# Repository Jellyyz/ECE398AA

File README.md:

<h1>Final Project</h1>

<h1>Midterm Project</h1>

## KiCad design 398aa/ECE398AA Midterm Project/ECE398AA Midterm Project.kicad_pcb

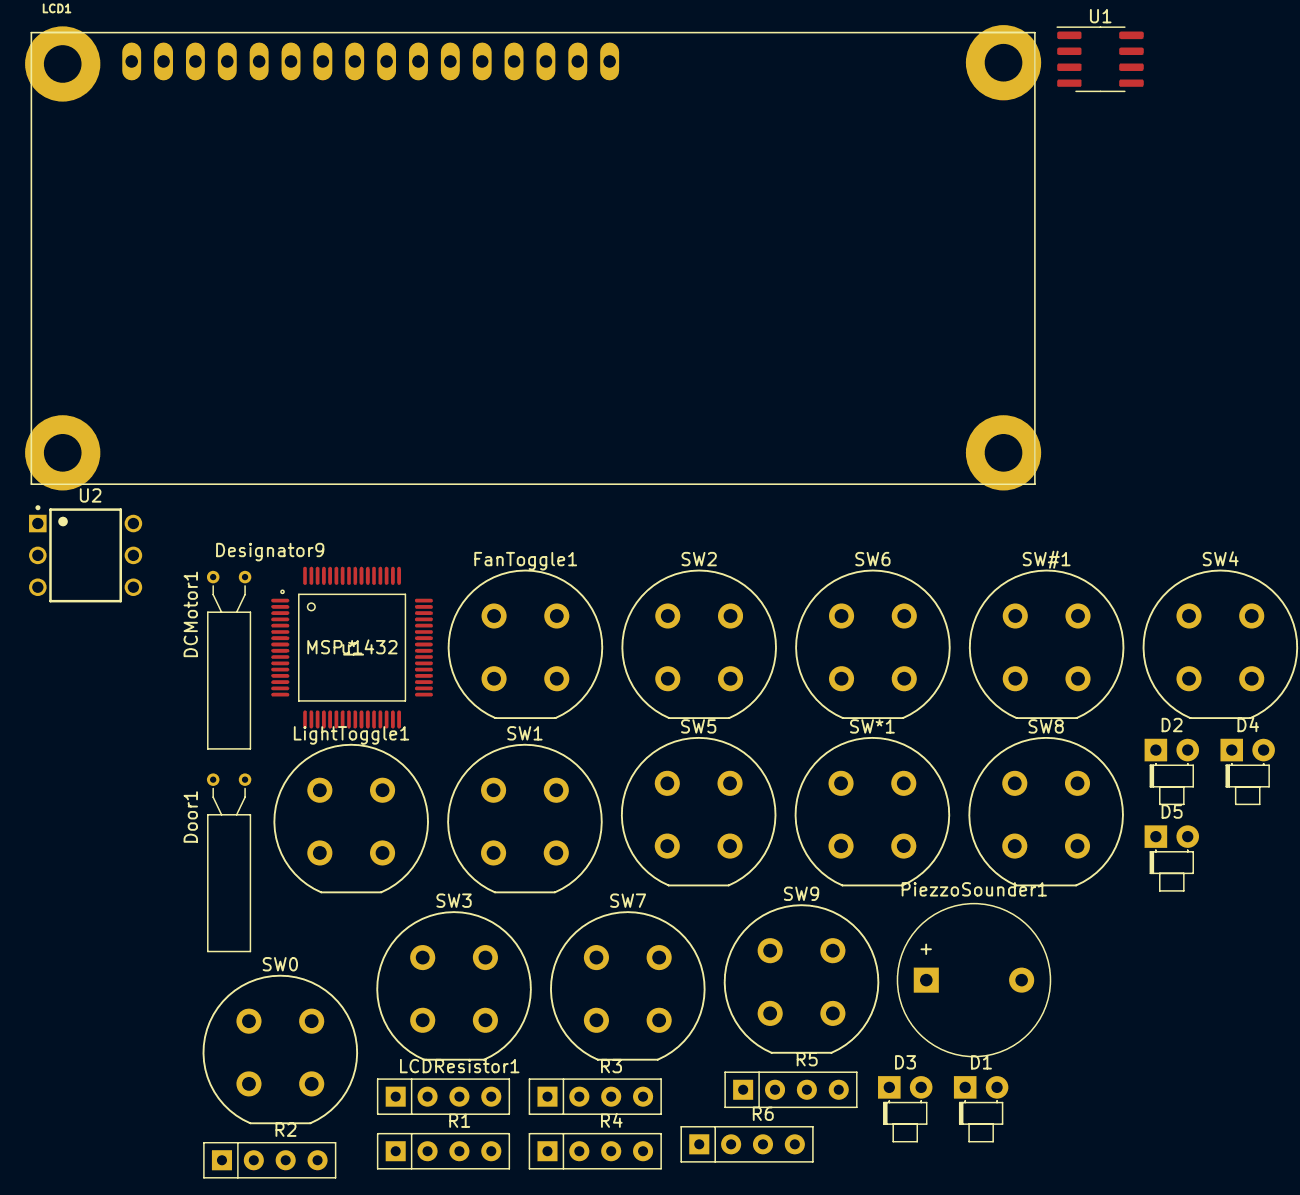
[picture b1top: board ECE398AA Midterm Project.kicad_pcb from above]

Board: 2 copper layers, 33 parts (0 on the bottom side), 14 nets, no tracks yet.

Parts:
D1, D2, D3: Yellow (House Lights); LED_D1.8mm_W1.8mm_H2.4mm_Horizontal_O1.27mm_Z1.6mm
D4: Door Open (Green); LED_D1.8mm_W1.8mm_H2.4mm_Horizontal_O1.27mm_Z1.6mm
D5: Door Close (Red); LED_D1.8mm_W1.8mm_H2.4mm_Horizontal_O1.27mm_Z1.6mm
DCMotor1: Fan1; Crystal_AT310_D3.0mm_L10.0mm_Horizontal
Door1: Motor_Servo; Crystal_AT310_D3.0mm_L10.0mm_Horizontal
FanToggle1: SW_Push; Push_E-Switch_KS01Q01
LCD1: HD44780; 16026-16X2
LCDResistor1: R_POT_US; R_Array_SIP4
LightToggle1: SW_Push; Push_E-Switch_KS01Q01
PiezzoSounder1: Buzzer; Buzzer_12x9.5RM7.6
R1, R2, R3, R4, R5: 330 Ω; R_Array_SIP4
R6: 300 Ω; R_Array_SIP4
SW0: 0; Push_E-Switch_KS01Q01
SW1: 1; Push_E-Switch_KS01Q01
SW2: 2; Push_E-Switch_KS01Q01
SW3: 3; Push_E-Switch_KS01Q01
SW4: 4; Push_E-Switch_KS01Q01
SW5: 5; Push_E-Switch_KS01Q01
SW6: 6; Push_E-Switch_KS01Q01
SW7: 7; Push_E-Switch_KS01Q01
SW8: 8; Push_E-Switch_KS01Q01
SW9: 9; Push_E-Switch_KS01Q01
SW#1: #; Push_E-Switch_KS01Q01
SW*1: *; Push_E-Switch_KS01Q01
U1: TMP36xS; SOIC-8_3.9x4.9mm_P1.27mm
U2: H11B1; DIP762W50P254L730H410Q6
u1: MSP__432; MSP430FR5994IPM

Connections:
GNDREF: D1.1, D2.1, D3.1, D4.1, D5.1
unnamed: D1.2, R1.2
unnamed: D2.2, R2.2
unnamed: D3.2, R3.2
unnamed: D4.2, R4.2
unnamed: D5.2, R5.2
unnamed: DCMotor1.1, Door1.2, R6.1
unnamed: DCMotor1.2, U2.5
unnamed: LCD1.P$1, LCD1.P$5, LCD1.P$15, LCDResistor1.3
unnamed: FanToggle1.1, LightToggle1.1, U1.4, U2.2, U2.4
unnamed: LCD1.P$3, LCDResistor1.2
unnamed: LCD1.P$2, LCD1.P$16, LCDResistor1.1
unnamed: R6.2, U1.8
unnamed: SW0.1, SW1.1, SW1.2, SW2.1, SW2.2, SW3.1, SW3.2, SW4.1, SW4.2, SW5.1, SW6.1, SW6.2, SW7.1, SW7.2, SW8.1, SW9.1, SW9.2, SW#1.1, SW#1.2, SW*1.1, SW*1.2

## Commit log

2021-12-09 final
2021-12-09 readme final

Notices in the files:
parts and their libraries:
Copyright 2021 Accelerated Designs. All rights reserved.
